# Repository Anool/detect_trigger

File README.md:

# detect_trigger
camera trigger hardware

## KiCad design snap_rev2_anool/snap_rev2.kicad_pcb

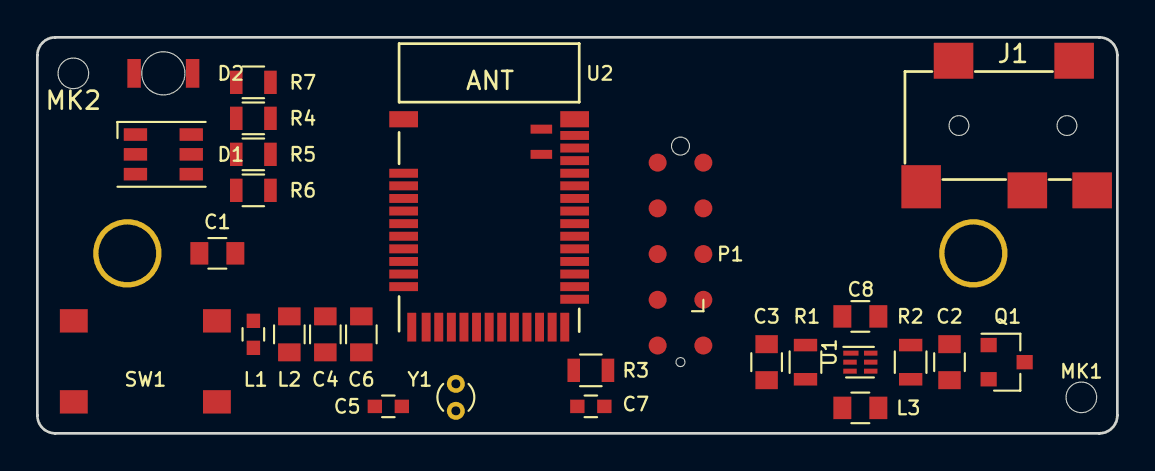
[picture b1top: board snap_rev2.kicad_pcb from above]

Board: 2 copper layers, 60.0 x 22.0 mm, 30 parts (1 on the bottom side), 31 nets, no tracks yet.

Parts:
BT1: AA battery; AA_keystone_206
C1, C4: 1u; C_0805
C2, C8: 10u; C_0805
C3, C6: 100n; C_0805
C5, C7: 8.2p; C_0603
D1: CLX6F-FKC; LED_RGB_PLCC-6
D2: IR26-21C-L110-TR8; IR26-21C-L110
J1: SJ2-35863B1; SJ2-35863B1-SMT
L1: 15n; C_0603
L2: 10u; C_0805
L3: 4.7u; C_0805
MK1, MK2: Mounting_Hole_PAD; MountingHole_1.7mm_M1.6
P1: CONN_02X05; prog_connect
Q1: TSM2301
R1, R3: 400; R_0805
R2: 47k; R_0805
R4: 82; R_0805
R5: 68; R_0805
R6: 33; R_0805
R7: 130; R_0805
SW1: 1825910-6; SMD_tactile_button
U1: TPS610986; WSON6_1.5x1.5mm_Pitch0.5mm
U2: MDBT42Q; mdbt42Q
Y1: 32786Hz; Crystal_DS10_d1.0mm_l4.3mm_Vertical

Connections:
/BUTTON: SW1.2, U2.26
/DCC: L2.2, U2.10
/DEC4: C1.1, L1.1, U2.9
/FOCUS: J1.2, U2.21
/GPIO1: P1.6, U2.32
/GPIO2: P1.8, U2.34
/JACK_DETECT: J1.10, R3.2, U2.22
/LED_BLUE: R4.1, U2.17
/LED_GREEN: R5.1, U2.19
/LED_RED: R6.1, U2.16
/LED_SENSE: D1.5, R5.2, U2.18
/LFCLK_XL1: C5.1, U2.13, Y1.1
/LFCLK_XL2: C7.1, U2.14, Y1.2
/REG_MODE: R2.1, U1.4, U2.3
/RESET: P1.5, U2.35
/RX: P1.2, U2.27
/SWDCLK: P1.4, U2.36
/SWDIO: P1.3, U2.37
/TRIGGER: J1.3, U2.20
/TX: P1.1, U2.31
/VBAT: C2.1, L3.1, Q1.3, R1.1, U2.5
GND: BT1.2, C1.2, C2.2, C3.2, C4.2, C5.2, C6.2, C7.2, C8.2, D1.1, D1.2, D1.3, J1.1, P1.9, P1.10, Q1.2, R2.2, SW1.1, U1.6, U2.1, U2.12, U2.24, U2.39
unnamed: BT1.1, Q1.1
unnamed: C3.1, R1.2, U1.3
unnamed: D1.4, R6.2
unnamed: D1.6, R4.2
unnamed: D2.1, U2.25
unnamed: D2.2, R7.2
unnamed: L1.2, L2.1
unnamed: L3.2, U1.2
VDD: C4.1, C6.1, C8.1, P1.7, R3.1, R7.1, U1.1, U2.11

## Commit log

2017-11-02 camera trigger anool version
2017-11-02 camera trigger anool version2
